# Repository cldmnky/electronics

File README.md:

# electronics
Electronics projects

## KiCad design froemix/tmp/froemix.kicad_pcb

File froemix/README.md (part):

# Froemix

Daisy Seed based Eurorack module. The design is split over two boards:

| Board | Contents | Status |
| --- | --- | --- |
| **base board** (`tmp/`, `tscircuit/`) | Daisy Seed, CD4051 ADC multiplexer, Eurorack power entry (+/-12V -> VCC/VEE, +5V, -10V reference), audio in/out buffers, CV in attenuverters, CV out drivers, sync in/out, opto isolated MIDI, OLED/microSD/PMOD headers, board-to-board headers | converted to tscircuit |
| **eurorack board** (`euro/`, `doc/EURO-BOARD.md`) | 20HP front board: 10 mono jacks + 2 TRS MIDI jacks, 6 pots, 5-way UI joystick, illuminated MODE button, 2 CV-output activity LEDs, 1.3" OLED, and the panel | designed, routed, gated; the electrical contract it must meet is [`doc/FRONTBOARD-INTERFACE.md`](doc/FRONTBOARD-INTERFACE.md) |

Inspiration: Electrosmith Daisy Patch (`~/Downloads/Patch-Design-Files-EAGLE`,
20HP, 19 jacks, SMT euro jacks + TRS MIDI).

The Daisy Seed module itself is already in hand, so it is marked `doNotPlace` and
kept out of the JLCPCB assembly.

## Repository layout

```
froemix/
├── tmp/                 original KiCad 10 project (frozen reference; layout lives in tscircuit/)
│   └── library/         jclpcb.pretty + official Electrosmith DaisyKiCad footprints
├── tools/
│   ├── kicad2tscircuit.py   KiCad -> tscircuit port baseline (retired as an editor)
│   ├── check_netlist.py     netlist vs KiCad (pin for pin)
│   ├── check_extras.py      tscircuit-only parts: pins, removed refs, pin moves
│   ├── check_footprints.py  footprints vs KiCad (pad for pad)
│   ├── check_parts.py       JLCPCB parts vs schematic (type, value, package)
│   ├── report_decoupling.py cap -> IC routed-copper distances (informational)
│   ├── lcsc_models.json     EasyEDA 3D models per LCSC code (harvested once)
│   └── sim/                 four ngspice decks + RESULTS.md (gain, CV, ref bias)
├── euro/                the 20HP front board + panel (tscircuit project)
│   ├── index.circuit.tsx    jacks, pots, OLED, LED + the 3 sockets that mate CN1/CN2/CN4
│   ├── panel.circuit.tsx    the front panel (holes + silkscreen, no copper)
│   ├── lib/layout.ts        ONE table of coordinates, imported by board and panel
│   ├── lib/footprints.tsx   XKB PJ-301M jack, Alps RK09K, sockets, OLED, LED
│   ├── panel/               built-artwork Nord/Signal previews and 1:1 fit templates
│   └── scripts/             board/panel gates and separate fabrication releases
├── tscircuit/           the base board design (hand-maintained)
│   ├── index.circuit.tsx    board outline + one <schematicsheet> per KiCad sheet
│   ├── sections/*.tsx       components per sheet, nets.tsx with all <net> elements,
│   │                        fabrication.tsx (fiducials/test points), silk.tsx
│   ├── lib/
│   │   ├── pins.ts          pin labels (KiCad pin number -> label) per IC
│   │   └── footprints.tsx   exact footprints for every part on the board
│   └── scripts/             gate.sh / release.sh (`bun run gate` / `release`)
├── firmware/            Daisy Seed firmware (M0 scaffold, never run on hardware yet)
│   ├── src/pins.hpp         board net -> Seed pin, checked against tscircuit/
│   ├── src/contracts.hpp    hardware contracts as constants + static asserts
│   ├── src/audio/audio6.*   6 channels: Seed SAI1 stereo + eurorack-pmod SAI2 TDM
│   ├── src/engine/          the engine seam (only a Silent implementation)
│   ├── src/hw/              ak4619, pmod, controls, cv, sync, midi, display
│   ├── patches/             the one local libDaisy change (SAI TDM slots)
│   └── scripts/             fetch_deps.sh (pinned libDaisy + DaisySP)
└── fab/                 release output (gitignored): gerbers, bom, pnp, svg, step
```

The KiCad port is done: `tscircuit/` is now the design itself — edit
`sections/*.tsx` and `index.circuit.tsx` directly (positions, widths, phases,
hints), preferably with `bun run dev` open for live feedback. Do NOT edit via
the generator anymore.

`tools/kicad2tscircuit.py` is retained as the port baseline plus the parsing
library the check scripts import (net names, pin labels, footprint/3D-model
maps, `EXTRA_COMPONENTS`, `PART_OVERRIDES`). `bun run regen:check` regenerates
into a temp dir and diffs against the tree: an empty diff means the design
still matches the ported schematics; any diff is exactly the set of direct
edits made since the port — review it, don't blindly overwrite either side.
The verification scripts (`check_netlist`, `check_footprints`, `check_parts`)
keep working unchanged: they compare the KiCad sources against the BUILT
`dist/index/circuit.json`, not against the generator.

## Printed board identity

The base, euro board and panel carry **Rev 0.1** and a UTC `YYYY-MM-DD` build
date on their rear faces. The base also carries the Nord monoline FROEMIX
wordmark, an OSHW gear and a short hand-build reminder. The gear is not a
certification mark; its attribution, share-alike notice and compliance caveat
are in [`assets/README.md`](assets/README.md).

`tsci dev` only serves files inside the project it is started in, so imports
from a common `shared/` directory break the browser preview even though a Node
build resolves them. The identity constants therefore live in both
`tscircuit/lib/build-info.ts` and `euro/lib/build-info.ts`, and the base's
`tscircuit/lib/wordmark.ts` mirrors the euro panel's `MONO_GLYPHS`. This is a
checked duplication, not a second source of truth: `tscircuit/scripts/test_silk.test.ts`
asserts both revisions and dates are equal and that the base's built wordmark is
byte-for-byte the euro geometry. A revision bump changes both files.

`make release` captures one date for all three outputs. Set
`FROEMIX_BUILD_DATE=2026-11-02 make release` to reproduce a dated set; use a
real calendar date. The snapshot gate deliberately uses `2024-08-10`, so
snapshots are stable and that reference date is **not** the release date.
Install both board projects with `make install`. Check the generated rear
silkscreens in the manufacturer preview; a successful gate is not CAM approval.

## Eurorack (front) board

The 20HP board that carries every panel control, plus its panel:

```bash
cd euro
bun install            # once
bun run dev            # live preview
bun run gate           # 10 steps: board + mux contract + panel art/tests + snapshots
```

It mates with the base board through CN1 (MIDI, muxed pot inputs, UI controls,
LED, rails), CN2 (the jack bus) and CN4 (display), on 2.00mm sockets on its
bottom side, at the base board's own frozen coordinates. CN3 (micro SD) is
intentionally not mated yet. `euro/scripts/check_mating.py` verifies, from the
built circuit JSON, that every socket pin lands on the base board's pin, that
all 22 panel parts sit exactly above their panel holes, that no panel hole is
orphaned, and that nothing is left unrouted.

The UI costs no extra wires: the 5-way joystick and the illuminated button sit
on the two muxed pot channels `M_ADC_6`/`M_ADC_7` as resistor ladders (see
`doc/EURO-BOARD.md` §2 and §7 — the ladder levels are a firmware contract). The two CV jack LEDs need no pins at all: each one is driven by its own jack
signal through a diode and a resistor. The four audio LEDs were removed because
their direct diode/LED load distorted the audio jacks.

Design record, floorplan and the open decisions (joystick sourcing, OLED
module, jack height, button part, CN3/SD, panel material):
[`doc/EURO-BOARD.md`](doc/EURO-BOARD.md).

### Faceplate design and fabrication

The panel-specific record is [doc/FRONT-PANEL.md](doc/FRONT-PANEL.md): material
comparison, two white-on-black design directions, JLCPCB order settings and a
first-article fit checklist. **Signal** is the selected direction for this
revision (`FROEMIX_PANEL_DESIGN=nord` builds the Nord alternative). Recommended
material is **2mm FR4 with standard
black solder mask and white print**, ordered separately from the electronic
boards, without assembly or a stencil. A Gerber check is not a physical-fit
approval. The corrected Z stack, cut-to-seven CN4 preparation, printable MODE/NAV
actuator prototypes and remaining physical acceptance tests are in
[`doc/MECHANICAL-STACK.md`](doc/MECHANICAL-STACK.md).

## Base board <-> eurorack board interface

`CN1`/`CN2` are 2.00mm 16-pin headers — now XKB **6mm-shoulder + 4mm-post**
`X4612WV-16I-C40D28-E60` (C2883069), with **11mm clear spacers**, mating the
existing 4.3mm front sockets. The old short `A2005WV-16P` cannot reach across
the stack. `CN2` is the jack bus, `CN1` carries MIDI, muxed ADC inputs and power.

| CN2 | net | CN1 | net |
| --- | --- | --- | --- |
| 1 | `J_AUDIO_IN_L` | 1 | `J_MIDI_IN_TIP` |
| 2 | `J_AUDIO_IN_R` | 2 | `J_MIDI_IN_RING` |
| 3 | `J_AUDIO_OUT_L` | 3 | `J_MIDI_OUT_TIP` |
| 4 | `J_AUDIO_OUT_R` | 4 | `J_MIDI_OUT_RING` |
| 5 | `J_SYNC_IN` | 5-12 | `M_ADC_0` .. `M_ADC_7` (muxed, for pots) |
| 6 | `J_SYNC_OUT` | 13 | `LED` |
| 7 | `J_CV_IN_1` | 14 | `P3V3_D` |
| 8 | `J_CV_IN_2` | 15 | `P3V3_A` |
| 9 | `J_CV_OUT_1` | 16 | `GND` |
| 10 | `J_CV_OUT_2` | | |
| 16 | `GND` | | |

Other headers: `CN3` micro SD, `CN4` OLED (SPI + DC/RES), `H1` PMOD (I2S + I2C),
`J1` MIDI 2x3 **polarity-select jumper block** (two shunts — not a socket;
**Type A = shunts 3–5 + 4–6**, **Type B = 4–2 + 3–1**, see
[`doc/ASSEMBLY.md`](doc/ASSEMBLY.md)), `J2` Eurorack 2x8 power. A 2.54 mm
shunt only bridges two pads 2.54 mm apart, so the diagonal 4–5 (3.59 mm) can
never be one of the pairs.

**Both MIDI directions are TRS Type A on this board**: the OUT socket is a Type
A transmitter (ring = current source through `R59` 22 Ω 1 W from `P3V3_D` behind
the `Q2` PNP high-side switch, tip = sink through `R60` 33 Ω to GND), and the
IN defaults to Type A with the `J1` shunts above. A straight-through panel
wiring (tip → tip, ring → ring) is correct for both; the alternative would have
been a Type B OUT, which needs a crossover.

The electrical contract for the front board (naming, limits, power budget and
its acceptance test) is [`doc/FRONTBOARD-INTERFACE.md`](doc/FRONTBOARD-INTERFACE.md):
`M_ADC_0…7` may only be driven by pot/attenuverter wipers powered from this
board's own `P3V3_A`/`GND`, inside 0–3.3 V in every power order.

## Verification

```bash
cd froemix/tscircuit
bun install

# `bun run regen` is RETIRED: it overwrites tscircuit/ with packer output.
bun run gate               # everything below + build + snapshot diff (CI entry point)
bun run check:erc          # KiCad ERC, 0 unexcluded errors/warnings
bun run check:netlist      # 102 nets must match the KiCad netlist
bun run check:extras       # tscircuit-only parts: pins, removed refs, pin moves
bun run check:footprints   # every pad: number, size, drill, position (429 pads)
bun run check:parts        # JLCPCB part numbers vs schematic (needs network)
bun run check:values       # TSX value literals vs built values and MPNs
bun run check:silk         # B/F silkscreen inside the board outline (gerbers)
bun run build              # tsci build -> dist/index/circuit.json
bun run check              # tsci check netlist (tscircuit source diagnostics)
bunx tsci check placement  # Errors 0, 1 known H1 warning
bunx tsci check shorts     # unintended copper shorts
bunx tsci check pcb-style  # odd-angle / staircase routing
bunx tsci snapshot --test --3d   # diff against __snapshots__/ (--update to accept)
bun run report:decoupling  # cap -> IC routed-copper distances
bun run release            # gate + fab export into ../fab
bun run dev                # interactive preview/editing
```

Current status: the gate is green (`bun run gate`, 15/15 steps). Netlist 102/102
nets, 429 pads match KiCad pad for pad (376 KiCad + 53 added; U16's four pads
are verified against the authored 2 W land pattern instead, see
`REPLACED_FOOTPRINTS`), `tsci check
netlist` Errors 0/Warnings 0, placement Errors 0 (plus the known H1 false
positive), shorts and pcb-style clean, silkscreen provably inside the outline,
routing 306 traces / 330 vias / 4948mm copper / 0 unconnected / 0 overlaps,
JLCPCB parts validated (117 components, 39 unique parts) and every passive
value literal checked against the built value. `bun run release` writes gerbers,
BOM, pick-and-place, schematic/PCB SVGs and STEP into `fab/`. What is still open
is listed under [Production readiness](#production-readiness).

**Firmware requirement:** the STM32H750 **DAC output buffer must be disabled**
(libDaisy `DacHandle::Config buff_state = DISABLED`, i.e. 0…VDDA output). The
CV-out stages are fed through unity-gain followers (U11A/U11D) so the unbuffered
DAC's ~13 kΩ output resistance does not cost gain; with the buffer enabled the
usable DAC range is 0.2…3.1 V and CV out cannot reach 0 V or full scale. See
[`doc/FRONTBOARD-INTERFACE.md`](doc/FRONTBOARD-INTERFACE.md) §4.

### Analog verification (SPICE)

Electrical checks that no layout tool can make: gain, bandwidth, CV scaling and
the reference bias current, simulated from the schematic values in
`tscircuit/sections/*.tsx`. Four standalone ngspice decks live in
`tools/sim/`, with the measured-vs-expected table and the findings in
[`tools/sim/RESULTS.md`](tools/sim/RESULTS.md):

```bash
cd froemix/tools/sim
bash run.sh            # needs ngspice (brew install ngspice); writes out/
```

| Chain | Result |
| --- | --- |
| Audio in (`J_AUDIO_IN_L` → ADC) | gain 0.1000 (−20.00 dB) as designed, −3 dB at **19.7 kHz** — two cascaded poles (100k ∥ 47pF, 10k ∥ 560pF), not the 28 kHz single-pole estimate |
| Audio out (DAC → `J_AUDIO_OUT_L`) | gain **3.300** (10.37 dB) after the R08 fix (R13/R14 feedback 33k), 3.2673 at the jack into 100k; −3 dB at **30.9 kHz** simulated with ideal opamps (30.0 kHz with the TL074 model) — the ×10 chain that clipped the ±11.7 V rails is gone |
| CV in (U13) | **0.3010 V/V, offset 1.6096 V**: ±5 V → **3.1146 / 0.1046 V**, no clipping anywhere in the sweep (R33/R42 30.1k, R34/R43 187k); worst 1 % corner 3.1775 / 0.0742 V, still 60 mV clear of the rails |
| CV out (U12) | **1.5121 V/V, load-independent**: 0…3.3 V DAC → 0…4.990 V at 100k, 50k, 10k and open, because the feedback pickup sits past the 1 k series resistor (R09) |
| −10 V reference (U14) | 0.809 mA cathode current at VEE = −12 V, worst case 0.445 mA over −11.2…−12.2 V, i.e. 3.6× the 125 µA design floor (4.45× the datasheet 100 µA typ) |
| Pitch error, 1 % vs 0.1 % resistors | 24 ¢/octave (CV in) and 48.5 ¢/octave worst case (CV out); 0.1 % parts give 2.4 / 4.8 ¢/octave plus fixed offsets |

None of these change the board: they confirm the design (audio gain, CV
scaling, reference bias) or document behaviour the firmware and the euro board
have to live with (the two audio roll-offs, the 1 % CV tolerance, the ±5 V CV
input limit). The simulation is not part of `bun run gate` and never touches
`dist/`.

### BOM fixes applied during conversion

The KiCad project still carries the old part numbers; the converter patches them
(`PART_OVERRIDES` in `tools/kicad2tscircuit.py`). Move them into KiCad and delete
the entries when convenient.

| Ref | Old | New | Why |
| --- | --- | --- | --- |
| R23 | `C728283` (1 mΩ 1 W current sense) | `C17927` `1206W4F1004T5E` (1 MΩ ±1%, **basic**) | schematic value is `1M`, the old part was a library leftover |
| C6, C7 | `C55393` `CL10C561JB8NNNC` | `C107054` `CC0603JRNPO9BN561` (560 pF NP0 ±5% 50 V) | old part is **discontinued, 0 stock** |
| J2 | none | `C3406` (2×8 2.54 mm IDC box header) | no JLCPCB part number in the KiCad BOM |
| CN1, CN2 | `C225268` `A2005WV-16P` (2mm shoulder) | `C2883069` `X4612WV-16I-C40D28-E60` (6mm total shoulder + 4mm post) | mechanical review: the old header could not enter the 4.3mm socket across the stack; pads/XY/nets unchanged |
| CN4 | `C225259` `A2005WV-7P` | `C2883061` `X4612WV-08I-C40D28-E60`, **cut to seven ways** | same 6mm stack; the stocked seven-way member (C2883060) did not resolve in JLC's catalogue |
| CN3 | `C225260` `A2005WV-8P` | `C22438291` `HX PZ2.0-1x8P ZZ` | only 131 pcs in stock |
| H1 | `C60565` `2.54-2*6PWZ` | `C22373932` `HC-PM254-8.5H-2x6PW` | only 62 pcs in stock; body depth 8.5 mm vs the 12.5 mm drawn in the footprint, same 2.54 mm pad grid |
| U16 | `C5365649` `B1205S-1WR3` (12V in, 1 W/200 mA) | `C5369484` `B2405S-2WR3` (24V in, **2 W/400 mA**) | input sees VCC−VEE ≈ 23.4V, double the 13.2V max; and the worst-case 5 V load (194 mA without the H1 module, 267 mA with it) does not fit 200 mA — see [`doc/POWER-BUDGET.md`](doc/POWER-BUDGET.md). Different package, so U16 also has its own footprint/placement |
| R48 | `C4216` 33k pull-up | `C4190` 2.2k | TLP2362 VO is open-collector; 33k is too slow for 31.25kbps MIDI |
| R29 | `C427297` 100R | `C21190` 1k | 5V/100R = 50mA into a short exceeds the TL074 drive; 1k like the other outs |
| C16, C21 | 100nF (48Hz LPF) | `C57112` 10nF NP0 (**basic**) | 100nF across the 30.1k CV-in leg kills audio-rate FM; 10nF = **529Hz** (1/(2π·30.1k·10n), was 482Hz against the old 33k), same class as the Patch reference |

`bun run check:parts` now reports all JLCPCB parts as matching the schematic.

### Value changes from the design review

The review (`doc/DESIGN-REVIEW.md`) changed these existing refs. The KiCad
project is frozen, so the changes live in `PART_OVERRIDES` /
`INTENTIONAL_PIN_MOVES` / `REMOVED_REFS` in `tools/kicad2tscircuit.py` and in
the tscircuit source.

| Ref | Change | Why |
| --- | --- | --- |
| R13, R14 | 100k → **33k** (`C4216`), gain ×10 → **×3.300** | R08: a 1 Vrms full-scale Seed output through ×10 asked for 14.1 V peak and clipped at ±10.1 V against ±11.7 V rails; ×3.3 is 4.62 V peak |
| R33, R42 | 33k → **30.1k** (`C23000`) | R10: the 33k/200k summer mapped ±5 V onto exactly 0/3.3 V, so the MCP6002 clipped both endpoints |
| R34, R43 | 200k → **187k** (`C22896`) | R10: offset leg, moves CV in to 0.104…3.114 V with 60 mV of rail headroom at the 1 % corners |
| D2 | **removed** (`C2128` 1N4148WS) | R01: it was in parallel with the U15 opto LED in the forward direction, so MIDI IN could never work. D1 (antiparallel) stays |
| R49, R50 | **removed** (33 Ω 0603 `C23140`, 100 mW) | R02: a grounded ring dissipates 330 mW. Replaced by the 1 W 2512 `R59`/`R60` around the new `Q2` PNP driver (next table), which also makes the OUT a **Type A** transmitter |
| U11A/U11D | spare TL074 channels rewired as **unity-gain followers** | R03: the unbuffered DAC is a ~13 kΩ source; the followers keep the 33k summing resistors from costing 28 % of the range (firmware must disable the DAC buffer). U11 pins 3/12 and R31/R32 pin 1 moved nets |
| R39, R40 | feedback pickup moved **past** the 1 k series resistor, plus **C33/C34 100 pF** across them | R09: 1 k outside the loop made CV gain load-dependent (−11.8 ¢/octave from one to two 100k inputs); the gain is now a load-independent 1.5121. Moving it inside the loop put the cable capacitance there too, so 100 pF per channel compensates that pole (stable to ~10 nF) |

### BOM notes

- 39 unique parts. The passives, diodes, the MMBT3904/MMBT3906 SOT-23s and the 10nF CV caps are
  JLCPCB library parts; there is no basic replacement for the TL074, CD4051,
  MCP6002, LM4040, TLP2362 or B2405S, so the extended-part fee applies to those
  (JLC shows the exact basic/extended split and the fee on the order page).
- `CN1`/`CN2` are now `C2883069` (198 pcs at selection, two per board); CN4's
  `C2883061` had 832 pcs. These are hand-fitted THT parts, not SMT-line stock.
  Re-check live stock before ordering a run; `check:parts` does not stock-plan.
- The H1 swap changes the right-angle header body depth (12.5 -> 8.5 mm). Same
  pad grid, but check it against the PMOD cable/enclosure before ordering.
- `DaisySeed1` is `doNotPlace` (module already in hand); `J2` has no
  manufacturer part number, only the LCSC number.

### Parts added in tscircuit (not yet in KiCad)

These exist only in the generated project (`EXTRA_COMPONENTS` in
`tools/kicad2tscircuit.py`). Mirror them into the KiCad schematics and remove
the entries when convenient. The netlist/footprint checks know about them, so
`bun run check:all` stays green.

| Ref | Part | Why |
| --- | --- | --- |
| C28 | 100nF 0603 `C14663`, P3V3_D–GND at U15 | TLP2362 datasheet: 0.1µF bypass pin6–pin4 within 1cm, mandatory |
| C29 | 100nF 0603 `C14663`, P3V3_D–GND | P3V3_D had no decoupling (only P3V3_A has C19) |
| C30 | 10µF 1206 `C13585`, P3V3_D–GND | P3V3_D bulk for SD/OLED current spikes |
| C31 | 100nF 0603 `C14663`, P3V3_A–GND at U1 | R06: U1 (CD4051) had no local bypass — C19 sits 25.6 mm away at U13. Now 7.71 mm of routed rail |
| C32 | 1µF/50V 0603 `C559769`, `U16_VIN_P`–`U16_VIN_N` | R13: the B2405S datasheet asks for 1 µF/50 V **at the input pins** (module pins 1/2, 2.64 mm of routed rail); C26 sits before L1/L2 and is not that cap |
| C33, C34 | 100pF C0G 0603 `C14665`, across R39/R40 (CV out 2 / CV out 1) | R09 follow-up: the in-loop 1 kΩ plus cable capacitance rang (~18° phase margin at 1 nF); the 100 pF zero at 15.9 kHz makes 1 nF and 10 nF loads clean (`tools/sim` deck 5) |
| Q2 | MMBT3906 **PNP** SOT-23 `C53444`, emitter `P3V3_D`, collector `NET_Q2_C` | R02: MIDI OUT high-side driver — off at UART idle (high/high-Z), on for the start bit, so the loop current is not inverted and the MCU pin never sits on the cable |
| R58 | 4.7k 0603 `C23162`, `USART1_TX` → Q2 base | R02: Q2 base resistor (~0.47 mA of base current with the UART low) |
| R59 | 22 Ω **1 W 2512** `C118189` (`FP_jclpcb_R2512`, authored here), `NET_Q2_C` → `J_MIDI_OUT_RING` | R02 + Type A: the MIDI OUT **current source** on the ring (DIN pin 4). 0.50 W into a ring shorted to GND on a 1 W part, and still 4.48 mA worst case into a receiver at 1.7 V Vf |
| R60 | 33 Ω **1 W 2512** `C53728`, `J_MIDI_OUT_TIP` → `GND` | R02 + Type A: the MIDI OUT **current sink** on the tip (DIN pin 5), no transistor in the return; 0.33 W if the tip is pulled to 3.3 V. Replaced the 100 mW 0603 R49/R50 |
| R61 | 10k 0603 `C25804`, `NET_Q2_B` → `P3V3_D` | R02 follow-up: holds the Q2 base at its emitter while `USART1_TX` is high-Z (reset/bootloader), so a floating UART cannot turn the source on |
| D5 | 1N4148WS SOD-323 `C2128`, cathode on `NET_Q1_1` | R04: clamps Q1's base-emitter, so a −10 V sync patch can no longer exceed the 6 V rating |
| R51, R52 | 4.7k 0603 `C23162`, SCL/SDA to P3V3_D | I2C needs pull-ups (cf. Patch R77/R89/R91) |
| R53–R57 | 47k 0603 `C25819`, SD_DAT0–3 + SD_CMD to P3V3_D | SD needs pull-ups (cf. Patch R3–R7 47K) |

`R13`/`R14` (audio feedback, 33k) and `R33`/`R34`/`R42`/`R43` (CV-in summer)
also belong here in spirit: they are existing KiCad refs whose **values**
changed, so they are `PART_OVERRIDES` rather than new components — see the
table above.

### Deliberately not changed

- **CV scaling resistors stay 1%.** ~2 % of scale on CV in and ~4.04 % worst
  case on CV out (24 ¢ and 48.5 ¢/octave, simulated), plus fixed offsets. 0.1 %
  replacements exist but none are JLCPCB basic, so this trades assembly cost for
  firmware calibration. Calibrate pitch in firmware; the CV-in endpoints no
  longer need a guard band in software (they now sit 60 mV inside the rails).
- **M_ADC mux inputs have no clamps.** The CD4051 runs at 0–3.3V; anything above
  ~3.8V damages U1 and the Seed ADCs (pins 24/25/28–30 are 3.3V-only, not 5V
  tolerant). That is now a written interface requirement for the euro board —
  pots/attenuverters powered from `P3V3_A`/`GND` only, `M_ADC_*` inside 0–3.3 V
  in every power-up/down order: [`doc/FRONTBOARD-INTERFACE.md`](doc/FRONTBOARD-INTERFACE.md)
  (finding R14).
- **No encoder counterpart.** The Patch reference has an encoder; the base board
  has no encoder pins. CN2 pads 11–15 are unconnected — reserve three for
  ENC_A/ENC_B/CLICK when the euro board is designed, or consciously drop it.
- H1 footprint body is 8.5mm deep (silk x 2.8…11.3), matching the fitted
  `HC-PM254-8.5H` part — the `W12.5` in the footprint name is just a name.
  (An older note claimed a 12.5→8.5mm mismatch; remeasured, no mismatch.)
- Pre-order checklist: use M3 standoffs/washers of <=5mm OD. The old note here
  claimed a 5.5mm-OD standoff reaches 0.3mm into J2's courtyard — that is wrong:
  the J2 courtyard edge is **3.96mm** from the (−36.95, −60.75) hole centre, so
  a 5.5mm-OD standoff (r = 2.75mm) **clears it by 1.2mm**. The tight holes are
  the other two: **C25** comes within 2.95mm of the (36.95, −60.75) hole and
  **CN1** within 3.05mm of the (−36.95, 60.75) hole, so ≤5mm OD is the hardware
  limit there (a 5.5mm standoff would sit on C25's courtyard). Also: sanity-check
  the CPL rotation/mirror mapping for bottom-side parts with JLC (classic
  bottom-mirror trap — 101 of the 107 bottom placements are at 180° and 6 at
  0°, but verify); 6x C1671 47pF caps emit
  `source_part_not_found_warning` (no EasyEDA 3D-model match — the LCSC part
  itself validates fine, they just render pad-only in 3D); the ~90
  `source_component_availability_warning`s are build-time data gaps, not BOM
  problems (`check_parts.py` is the authority and passes); silkscreen refdes
  exist for every IC/module, connector, electrolytic and diode plus `FROEMIX`,
  `REV 0.1`, the date and the hand-solder legend (31 texts,
  `sections/silk.tsx`) — the 0603/1206 passives stay unlabelled, assemble them
  from the CPL.

## JLCPCB order

`bun run release` produces everything the JLCPCB order page needs, including
JLC-shaped assembly files (their SMT line takes a BOM and a CPL, not the
per-designator exports tscircuit writes natively):

| Board | Upload | File |
| --- | --- | --- |
| base | Gerbers | `fab/froemix-gerbers.zip` |
| base | BOM (JLC) | `fab/froemix-bom-jlc.csv` - all 38 parts, for reference |
| base | BOM (upload) | **`fab/froemix-bom-smt.csv`** - only the 31 parts JLCPCB places |
| base | BOM (hand) | **`fab/froemix-bom-hand.csv`** - the 8 parts you solder yourself, as a shopping list |
| base | CPL | `fab/froemix-cpl-jlc.csv` (107 SMT placements) |
| euro | Gerbers | `fab/euro/euro-gerbers.zip` |
| euro | BOM (upload) | **`fab/euro/euro-bom-smt.csv`** - 5 unique parts, 12 placements |
| euro | BOM (hand) | **`fab/euro/euro-bom-hand.csv`** - 9 unique parts, 27 through-hole |
| euro | CPL | `fab/euro/euro-cpl-jlc.csv` (12 SMT placements) |
| euro panel | Gerbers | `fab/euro/panel/panel-gerbers.zip` (2 mm FR4, holes + silkscreen only) |

`make release` produces both sets in one run (`fab/` for the base board,
`fab/euro/` for the front board and panel).
| Reference | `fab/froemix-pnp-all.csv`, `fab/froemix-bom.csv`, SVGs, `froemix.step` |

Hand-mount instructions for everything JLC does not place (10 through-hole
board parts, two separately sourced 1×20 female Daisy socket strips, two `J1`
jumper shunts and the plug-in Daisy module): [`doc/ASSEMBLY.md`](doc/ASSEMBLY.md).
The sockets and shunts are not in the generated hand BOM; no socket part has
been selected or physically validated. The base-board finish is lead-free HASL.

Electrical contract for the front (euro/panel) board — connector pinout, CV and
audio levels, the `M_ADC` restriction and the 3.3 V budget:
[`doc/FRONTBOARD-INTERFACE.md`](doc/FRONTBOARD-INTERFACE.md).

Full guide, including THT hand soldering, single-sided bottom SMT assembly, the
bottom-rotation check and the order-day checklist:
[`doc/JLC-ASSEMBLY.md`](doc/JLC-ASSEMBLY.md) (also copied into `fab/`).

## Production readiness

| State | Item |
| --- | --- |
| done | **Copper width policy** — board floor 0.25mm, nothing on the board is thinner (rails 0.3–0.6mm) |
| done | **Silkscreen** — 31 texts: IC/connector/electrolytic/diode refdes, `FROEMIX`, `REV 0.1`, date, hand-solder legend; every glyph is provably inside the outline (gate step 14) |
| done | **Fiducials** — 4 FID pads, bottom side in the corner keepouts: bare copper with a 0.5mm mask window and no paste (verified in `B_Cu`+`B_Mask`, absent from `B_Paste`). `<fiducial>` itself exports mask-covered pads in this version, so they are one-pad footprints instead |
| done | **Test points** — 8 bottom-side TP pads: P5V, P3V3_D, P3V3_A, VCC, VEE, N10V_REF, SYNC_IN, MULTIPLEX_ADC_1 |
| done | **Decoupling** — every IC rail leg ≤11.8mm of routed copper (VCC/VEE legs), U1 now has its own C31 at 7.71mm; C14/C15 7.87/2.89mm; bulk C1 11.80mm / C30 19.09mm. GND legs are measured to the IC's return pin (U13 VSS 36.19mm); a dual-supply part whose return is the other rail (the TL074s' VMINUS on VEE) reports `-` instead of a grounded signal input — see AGENTS.md §3 |
| done | **Gates** — 15 steps: ERC, build, netlist, tscircuit-only parts (`check:extras`), footprints, JLCPCB parts, passive value literals, source/pin_spec/netlist, placement, shorts, pcb-style, silkscreen bounds, snapshot diff behind `bun run gate` |
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
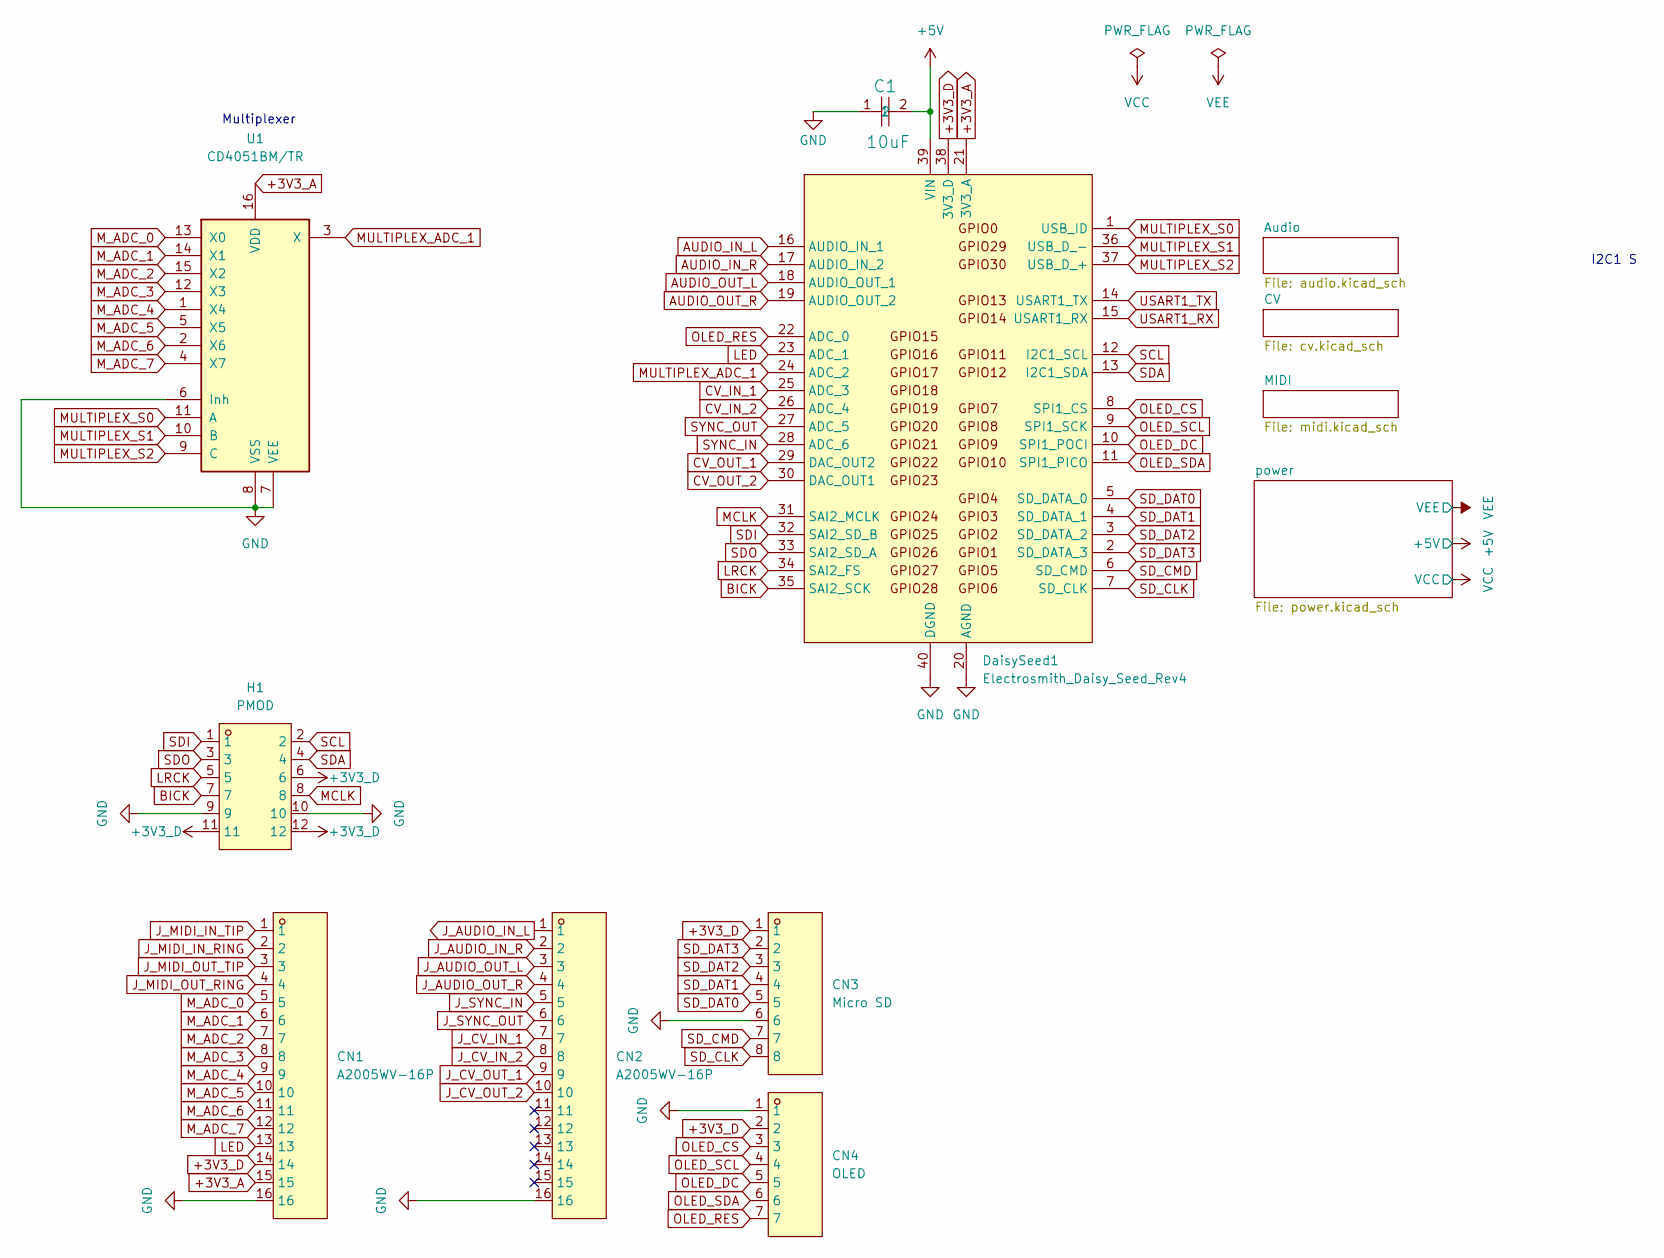
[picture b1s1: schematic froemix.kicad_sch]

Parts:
C1: 10uF; C1206; Part Number C3216X6S1V106K160AC; JLCPCB ID C13585
CN1, CN2: A2005WV-16P; HDR-TH_16P-P2.00-V-M; LCSC Part C225268
CN3: Micro SD; HDR-TH_8P-P2.00-V-M; LCSC Part C225260
CN4: OLED; HDR-TH_7P-P2.00-V-M; LCSC Part C225259
DaisySeed1: Electrosmith_Daisy_Seed_Rev4; Electrosmith_Daisy_Seed
H1: PMOD; HDR-TH_12P-P2.54-H-M-R2-C6-S2.54-W12.5; LCSC Part C60565
U1: CD4051BM/TR; SOP-16_L9.9-W3.9-P1.27-LS6.1-BL; LCSC Part C507163

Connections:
+3V3_A: CN1.15, DaisySeed1.21 (3V3_A), U1.16 (VDD); also elsewhere on the board
+3V3_D: CN1.14, CN3.1, CN4.2, DaisySeed1.38 (3V3_D), H1.6, H1.11, H1.12; also elsewhere on the board
+5V: C1.2, DaisySeed1.39 (VIN); also elsewhere on the board
AUDIO_IN_L: DaisySeed1.16 (AUDIO_IN_1); also elsewhere on the board
AUDIO_IN_R: DaisySeed1.17 (AUDIO_IN_2); also elsewhere on the board
AUDIO_OUT_L: DaisySeed1.18 (AUDIO_OUT_1); also elsewhere on the board
AUDIO_OUT_R: DaisySeed1.19 (AUDIO_OUT_2); also elsewhere on the board
BICK: DaisySeed1.35 (SAI2_SCK), H1.7
CV_IN_1: DaisySeed1.25 (ADC_3); also elsewhere on the board
CV_IN_2: DaisySeed1.26 (ADC_4); also elsewhere on the board
CV_OUT_1: DaisySeed1.29 (DAC_OUT2); also elsewhere on the board
CV_OUT_2: DaisySeed1.30 (DAC_OUT1); also elsewhere on the board
GND: C1.1, CN1.16, CN2.16, CN3.6, CN4.1, DaisySeed1.20 (AGND), DaisySeed1.40 (DGND), H1.9, H1.10, U1.6 (Inh), U1.7 (VEE), U1.8 (VSS); also elsewhere on the board
J_AUDIO_IN_L: CN2.1; also elsewhere on the board
J_AUDIO_IN_R: CN2.2; also elsewhere on the board
J_AUDIO_OUT_L: CN2.3; also elsewhere on the board
J_AUDIO_OUT_R: CN2.4; also elsewhere on the board
J_CV_IN_1: CN2.7; also elsewhere on the board
J_CV_IN_2: CN2.8; also elsewhere on the board
J_CV_OUT_1: CN2.9; also elsewhere on the board
J_CV_OUT_2: CN2.10; also elsewhere on the board
J_MIDI_IN_RING: CN1.2; also elsewhere on the board
J_MIDI_IN_TIP: CN1.1; also elsewhere on the board
J_MIDI_OUT_RING: CN1.4; also elsewhere on the board
J_MIDI_OUT_TIP: CN1.3; also elsewhere on the board
J_SYNC_IN: CN2.5; also elsewhere on the board
J_SYNC_OUT: CN2.6; also elsewhere on the board
LED: CN1.13, DaisySeed1.23 (ADC_1)
LRCK: DaisySeed1.34 (SAI2_FS), H1.5
MCLK: DaisySeed1.31 (SAI2_MCLK), H1.8
MULTIPLEX_ADC_1: DaisySeed1.24 (ADC_2), U1.3 (X)
MULTIPLEX_S0: DaisySeed1.1 (USB_ID), U1.11 (A)
MULTIPLEX_S1: DaisySeed1.36 (USB_D_-), U1.10 (B)
MULTIPLEX_S2: DaisySeed1.37 (USB_D_+), U1.9 (C)
M_ADC_0: CN1.5, U1.13 (X0)
M_ADC_1: CN1.6, U1.14 (X1)
M_ADC_2: CN1.7, U1.15 (X2)
M_ADC_3: CN1.8, U1.12 (X3)
M_ADC_4: CN1.9, U1.1 (X4)
M_ADC_5: CN1.10, U1.5 (X5)
M_ADC_6: CN1.11, U1.2 (X6)
M_ADC_7: CN1.12, U1.4 (X7)
OLED_CS: CN4.3, DaisySeed1.8 (SPI1_CS)
OLED_DC: CN4.5, DaisySeed1.10 (SPI1_POCI)
OLED_RES: CN4.7, DaisySeed1.22 (ADC_0)
OLED_SCL: CN4.4, DaisySeed1.9 (SPI1_SCK)
OLED_SDA: CN4.6, DaisySeed1.11 (SPI1_PICO)
SCL: DaisySeed1.12 (I2C1_SCL), H1.2
SDA: DaisySeed1.13 (I2C1_SDA), H1.4
SDI: DaisySeed1.32 (SAI2_SD_B), H1.1
SDO: DaisySeed1.33 (SAI2_SD_A), H1.3
SD_CLK: CN3.8, DaisySeed1.7 (SD_CLK)
SD_CMD: CN3.7, DaisySeed1.6 (SD_CMD)
SD_DAT0: CN3.5, DaisySeed1.5 (SD_DATA_0)
SD_DAT1: CN3.4, DaisySeed1.4 (SD_DATA_1)
SD_DAT2: CN3.3, DaisySeed1.3 (SD_DATA_2)
SD_DAT3: CN3.2, DaisySeed1.2 (SD_DATA_3)
SYNC_IN: DaisySeed1.28 (ADC_6); also elsewhere on the board
SYNC_OUT: DaisySeed1.27 (ADC_5); also elsewhere on the board
USART1_RX: DaisySeed1.15 (USART1_RX); also elsewhere on the board
USART1_TX: DaisySeed1.14 (USART1_TX); also elsewhere on the board

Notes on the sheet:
I2C1 S
Multiplexer

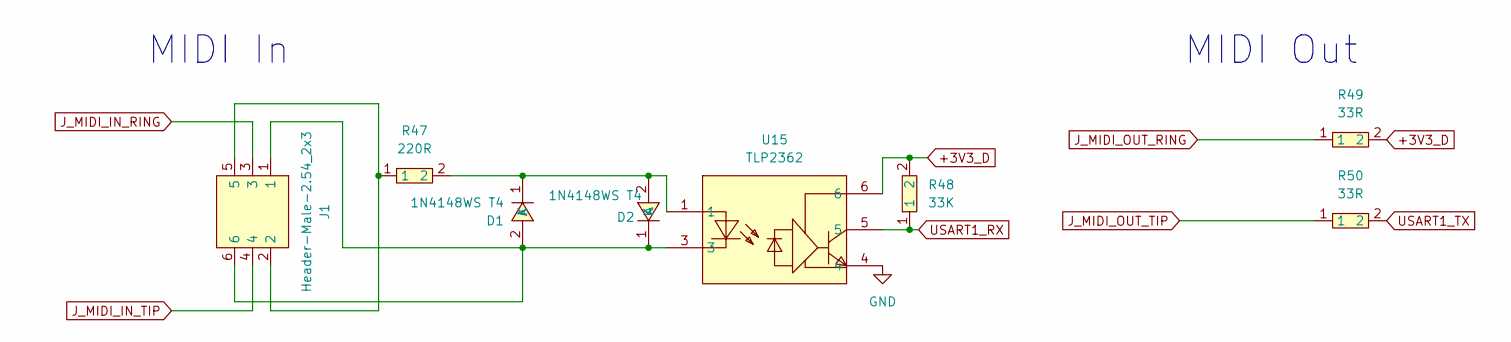
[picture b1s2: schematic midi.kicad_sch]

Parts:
D1, D2: 1N4148WS T4; SOD-323_L1.8-W1.3-LS2.5-RD; LCSC Part C2128
J1: Header-Male-2.54_2x3; HDR-TH_6P-P2.54-V-M-R2-C3-S2.54-1; LCSC Part C65114
R47: 220R; R0603; LCSC Part C22962
R48: 33K; R0603; LCSC Part C4216
R49, R50: 33R; R0603; LCSC Part C23140
U15: TLP2362; OPTO-SMD-5_L3.7-W4.6-P1.27-LS7.0-BR; LCSC Part C37658

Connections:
+3V3_D: R48.2, R49.2, U15.6; also elsewhere on the board
GND: U15.4; also elsewhere on the board
J_MIDI_IN_RING: J1.3; also elsewhere on the board
J_MIDI_IN_TIP: J1.4; also elsewhere on the board
J_MIDI_OUT_RING: R49.1; also elsewhere on the board
J_MIDI_OUT_TIP: R50.1; also elsewhere on the board
unnamed: D1.2 (A), D2.1 (K), J1.1, J1.6, U15.3
unnamed: D1.1 (K), D2.2 (A), R47.2, U15.1
unnamed: J1.2, J1.5, R47.1
USART1_RX: R48.1, U15.5; also elsewhere on the board
USART1_TX: R50.2; also elsewhere on the board

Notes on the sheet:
MIDI In
MIDI Out

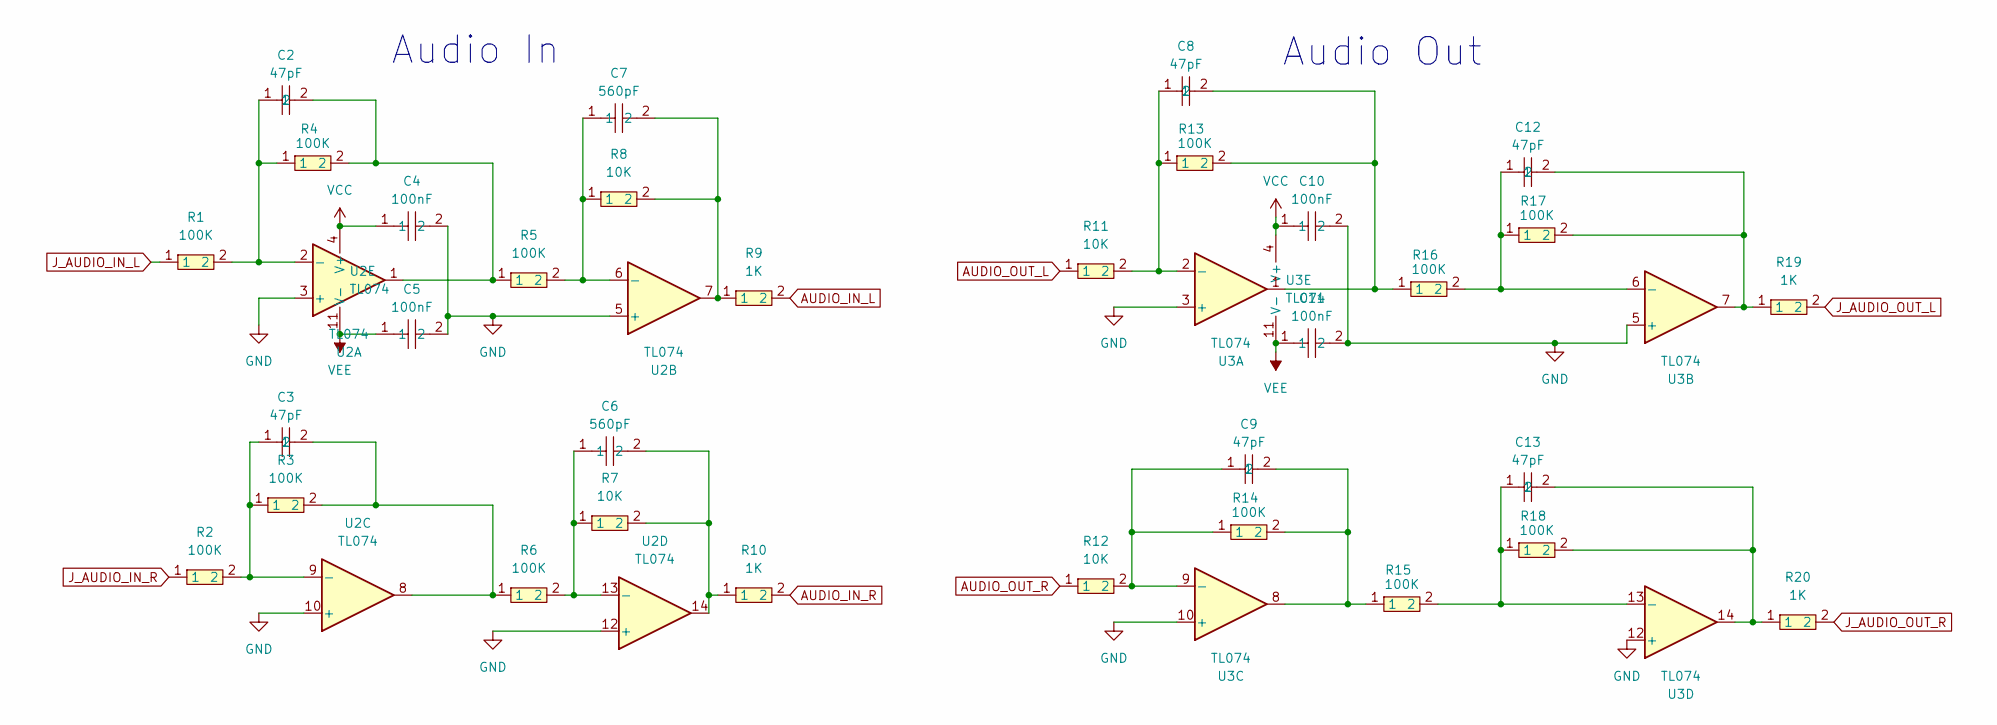
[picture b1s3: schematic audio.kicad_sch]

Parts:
C2, C3, C8, C9, C12, C13: 47pF; C0603; LCSC Part C1671
C4, C5, C10, C11: 100nF; C0603; LCSC Part C14663
C6, C7: 560pF; C0603; LCSC Part C55393
R1, R2, R3, R4, R5, R6, R13, R14, R15, R16, R17, R18: 100K; R0603; LCSC Part C25803
R7, R8, R11, R12: 10K; R0603; LCSC Part C25804
R9, R10, R19, R20: 1K; R0603; LCSC Part C21190
U2, U3: TL074; TSSOP-14_L5.0-W4.4-P0.65-LS6.4-BL; LCSC Part C96507

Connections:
AUDIO_IN_L: R9.2; also elsewhere on the board
AUDIO_IN_R: R10.2; also elsewhere on the board
AUDIO_OUT_L: R11.1; also elsewhere on the board
AUDIO_OUT_R: R12.1; also elsewhere on the board
GND: C4.2, C5.2, C10.2, C11.2, U2.3 (+), U2.5 (+), U2.10 (+), U2.12 (+), U3.3 (+), U3.5 (+), U3.10 (+), U3.12 (+); also elsewhere on the board
J_AUDIO_IN_L: R1.1; also elsewhere on the board
J_AUDIO_IN_R: R2.1; also elsewhere on the board
J_AUDIO_OUT_L: R19.2; also elsewhere on the board
J_AUDIO_OUT_R: R20.2; also elsewhere on the board
unnamed: C2.2, R4.2, R5.1, U2.1
unnamed: C3.2, R3.2, R6.1, U2.8
unnamed: C6.2, R7.2, R10.1, U2.14
unnamed: C7.2, R8.2, R9.1, U2.7
unnamed: C8.2, R13.2, R16.1, U3.1
unnamed: C9.2, R14.2, R15.1, U3.8
unnamed: C12.2, R17.2, R19.1, U3.7
unnamed: C13.2, R18.2, R20.1, U3.14
unnamed: C2.1, R1.2, R4.1, U2.2 (-)
unnamed: C7.1, R5.2, R8.1, U2.6 (-)
unnamed: C3.1, R2.2, R3.1, U2.9 (-)
unnamed: C6.1, R6.2, R7.1, U2.13 (-)
unnamed: C8.1, R11.2, R13.1, U3.2 (-)
unnamed: C12.1, R16.2, R17.1, U3.6 (-)
unnamed: C9.1, R12.2, R14.1, U3.9 (-)
unnamed: C13.1, R15.2, R18.1, U3.13 (-)
VCC: C4.1, C10.1, U2.4 (V+), U3.4 (V+); also elsewhere on the board
VEE: C5.1, C11.1, U2.11 (V-), U3.11 (V-); also elsewhere on the board

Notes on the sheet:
Audio Out
Audio In

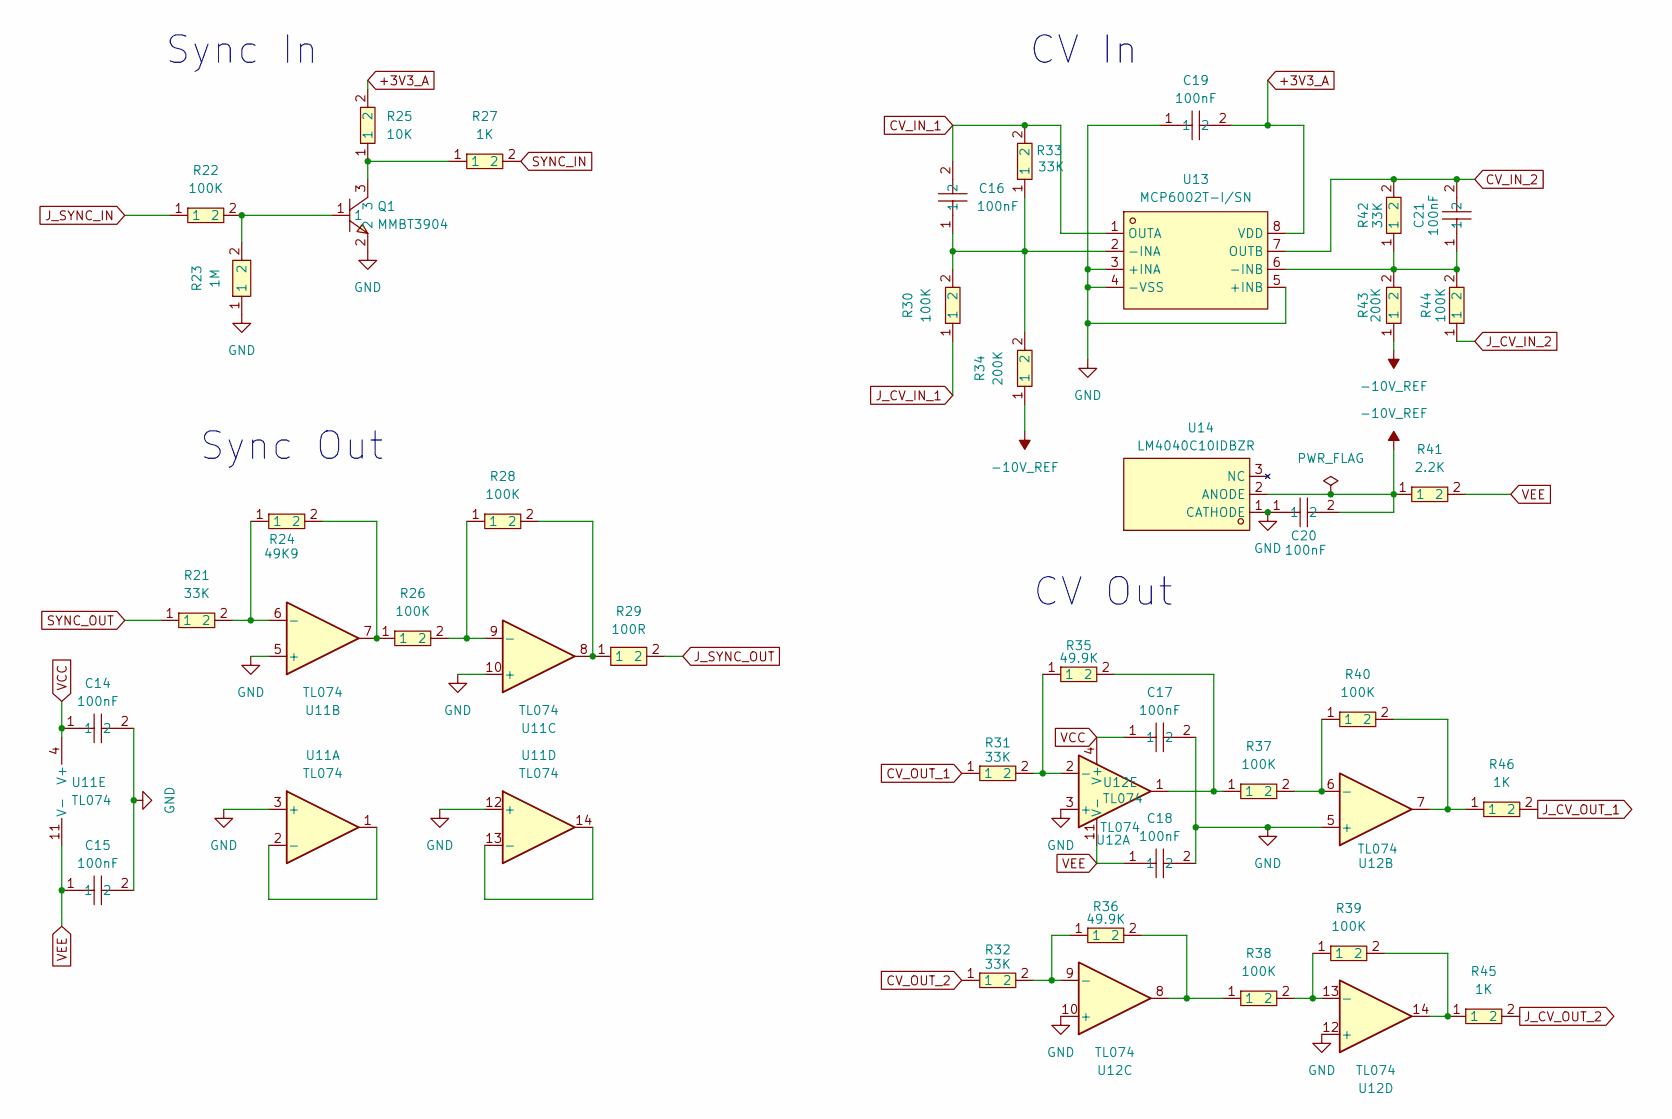
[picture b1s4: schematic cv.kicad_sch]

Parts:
C14, C15, C16, C17, C18, C19, C20, C21: 100nF; C0603; LCSC Part C14663
Q1: MMBT3904; SOT-23-3_L2.9-W1.6-P1.90-LS2.8-BR; LCSC Part C181119
R21, R31, R32, R33, R42: 33K; R0603; LCSC Part C4216
R22, R26, R28, R30, R37, R38, R39, R40, R44: 100K; R0603; LCSC Part C25803
R23: 1M; R1206; LCSC Part C728283
R24: 49K9; R0603; LCSC Part C23184
R25: 10K; R0603; LCSC Part C25804
R27, R45, R46: 1K; R0603; LCSC Part C21190
R29: 100R; R0603; LCSC Part C427297
R34, R43: 200K; R0603; LCSC Part C25811
R35, R36: 49.9K; R0603; LCSC Part C23184
R41: 2.2K; R0603; LCSC Part C4190
U11, U12: TL074; TSSOP-14_L5.0-W4.4-P0.65-LS6.4-BL
U13: MCP6002T-I/SN; SOIC-8_L4.9-W3.9-P1.27-LS6.0-BL; LCSC Part C7377
U14: LM4040C10IDBZR; SOT-23-3_L3.0-W1.7-P0.95-LS2.9-BR; LCSC Part C201738

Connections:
+3V3_A: C19.2, R25.2, U13.8 (VDD); also elsewhere on the board
-10V_REF: C20.2, R34.1, R41.1, R43.1, U14.2 (ANODE)
CV_IN_1: C16.2, R33.2, U13.1 (OUTA); also elsewhere on the board
CV_IN_2: C21.2, R42.2, U13.7 (OUTB); also elsewhere on the board
CV_OUT_1: R31.1; also elsewhere on the board
CV_OUT_2: R32.1; also elsewhere on the board
GND: C14.2, C15.2, C17.2, C18.2, C19.1, C20.1, Q1.2, R23.1, U11.3 (+), U11.5 (+), U11.10 (+), U11.12 (+), U12.3 (+), U12.5 (+), U12.10 (+), U12.12 (+), U13.3 (+INA), U13.4 (-VSS), U13.5 (+INB), U14.1 (CATHODE); also elsewhere on the board
J_CV_IN_1: R30.1; also elsewhere on the board
J_CV_IN_2: R44.1; also elsewhere on the board
J_CV_OUT_1: R46.2; also elsewhere on the board
J_CV_OUT_2: R45.2; also elsewhere on the board
J_SYNC_IN: R22.1; also elsewhere on the board
J_SYNC_OUT: R29.2; also elsewhere on the board
unnamed: Q1.1, R22.2, R23.2
unnamed: Q1.3, R25.1, R27.1
unnamed: R24.2, R26.1, U11.7
unnamed: R28.2, R29.1, U11.8
unnamed: R35.2, R37.1, U12.1
unnamed: R36.2, R38.1, U12.8
unnamed: R39.2, R45.1, U12.14
unnamed: R40.2, R46.1, U12.7
unnamed: U11.1, U11.2 (-)
unnamed: R21.2, R24.1, U11.6 (-)
unnamed: R26.2, R28.1, U11.9 (-)
unnamed: U11.13 (-), U11.14
unnamed: R31.2, R35.1, U12.2 (-)
unnamed: R37.2, R40.1, U12.6 (-)
unnamed: R32.2, R36.1, U12.9 (-)
unnamed: R38.2, R39.1, U12.13 (-)
unnamed: C16.1, R30.2, R33.1, R34.2, U13.2 (-INA)
unnamed: C21.1, R42.1, R43.2, R44.2, U13.6 (-INB)
SYNC_IN: R27.2; also elsewhere on the board
SYNC_OUT: R21.1; also elsewhere on the board
VCC: C14.1, C17.1, U11.4 (V+), U12.4 (V+); also elsewhere on the board
VEE: C15.1, C18.1, R41.2, U11.11 (V-), U12.11 (V-); also elsewhere on the board

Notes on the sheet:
Sync In
CV In
CV Out
Sync Out

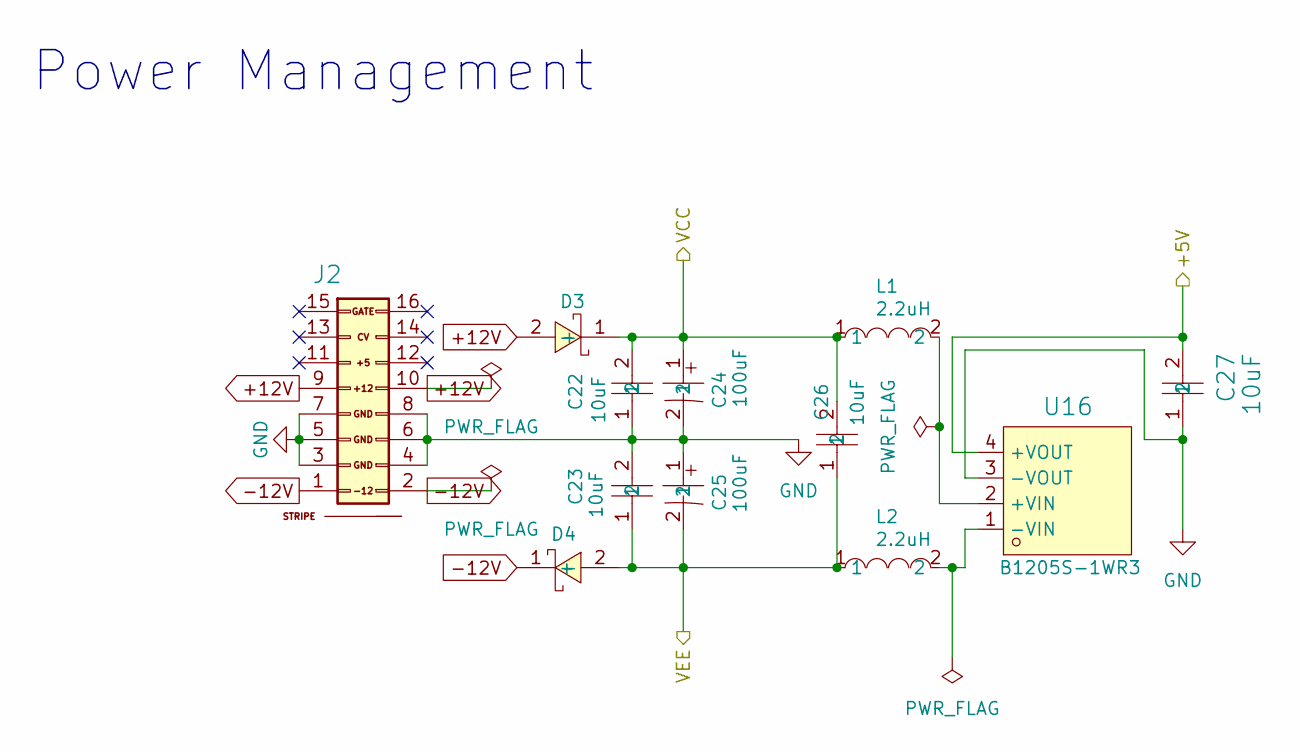
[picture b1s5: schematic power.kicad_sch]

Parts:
1, 2: PWR_FLAG
C22, C26, C27: 10uF; C1206; LCSC Part C13585
C23: 10uF; C1206; Part Number C3216X6S1V106K160AC; JLCPCB ID C13585
C24, C25: 100uF; CAP-TH_BD8.0-P3.50-D0.6-FD; LCSC Part C2749
D3, D4: B5819W_C8598; SOD-123_L2.7-W1.6-LS3.7-RD-1; LCSC Part C8598
J2: Eurorack Power 16 Pin IDC; Pins_2x08_2.54mm_TH_EurorackPower_Shrouded; Part Number LL1007-1 (2*8 HITEMP)
L1, L2: 2.2uH; L0603; LCSC Part C76797
U16: B1205S-1WR3; PWRM-TH_4P-L11.5-W6.0-P2.54_B1503S; LCSC Part C5365649

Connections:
+5V: C27.2, U16.4 (+VOUT); also elsewhere on the board
+12V: 1.1, D3.2 (+), J2.9 (+12V), J2.10 (+12V)
-12V: 2.1, D4.1 (-), J2.1 (-12V), J2.2 (-12V)
GND: C22.1, C23.2, C24.2, C25.1, C27.1, J2.3 (GND), J2.4 (GND), J2.5 (GND), J2.6 (GND), J2.7 (GND), J2.8 (GND), U16.3 (-VOUT); also elsewhere on the board
unnamed: L1.2, U16.2 (+VIN)
unnamed: L2.2, U16.1 (-VIN)
VCC: C22.2, C24.1, C26.2, D3.1 (-), L1.1; also elsewhere on the board
VEE: C23.1, C25.2, C26.1, D4.2 (+), L2.1; also elsewhere on the board

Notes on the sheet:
Power Management

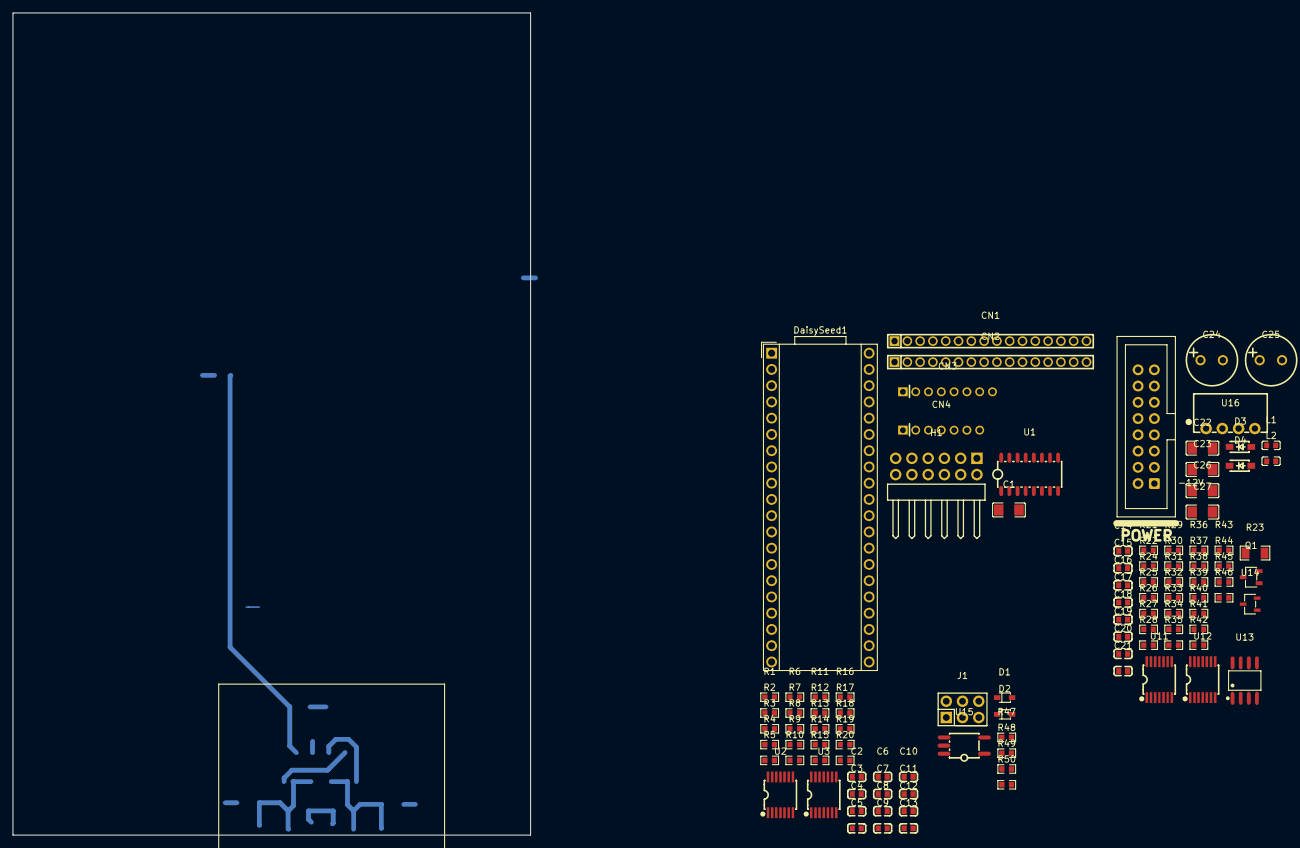
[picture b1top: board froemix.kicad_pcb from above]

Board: 4 copper layers, 80.9 x 128.5 mm, 101 parts (0 on the bottom side), 105 nets.

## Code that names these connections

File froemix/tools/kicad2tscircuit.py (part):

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    # instead of a spur crossing the Seed's footprint (SD_DAT0 alone cost
    # 104mm routed for a 25mm span). x > 10 is left clear for the CN4 ->
    # SPI1/I2C0 fanout and the audio pins, x < -22 for the MIDI_IN pair.
    "R56": (-18.0, 51.8),  # SD_DAT3: Seed -21.36 <-> CN3.pin2 3.14
    "R55": (-14.5, 51.8),  # SD_DAT2: Seed -18.82 <-> CN3.pin3 5.14
    "R54": (-11.0, 51.8),  # SD_DAT1: Seed -16.28 <-> CN3.pin4 7.14
    "R53": (-7.5, 51.8),  # SD_DAT0: Seed -13.74 <-> CN3.pin5 9.14
    "R57": (-4.0, 51.8),  # SD_CMD: Seed -11.20 <-> CN3.pin7 13.14
    "R51": (6.5, 51.8),  # SCL: Seed 4.04 <-> H1 29.77 (pull-up)
    "R52": (10.0, 51.8),  # SDA: Seed 6.58 <-> H1 29.77 (pull-up)
    # R50 is in series on Seed.USART1_TX <-> CN1.pin3 (J_MIDI_OUT_TIP) and
    # R49 pulls CN1.pin4 (J_MIDI_OUT_RING) to P3V3_D; both sat in the midi
    # island 120mm from CN1. Upper row so the R50 leg does not run across the
    # SD pull-up row.
    "R50": (-1.0, 55.4),
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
